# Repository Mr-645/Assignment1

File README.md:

Prab Singh - 2121645<br>MG7013 - Embedded Systems<br>16 May 2019
# Assignment 1 - Bubble display
## USAGE INSTRUCTIONS
1. Download and install the [Adafruit BMP085 Library](https://github.com/adafruit/Adafruit-BMP085-Library) for use with your Arduino compatible board.
2. If your setup is like mine (MOSFETs for the cathodes), find the `SevSeg.cpp` file of library and make [these](https://github.com/Mr-645/Assignment1#changes-to-sevsegcpp) modifications.
3. Download [this folder](https://github.com/Mr-645/Assignment1/tree/master/Assignment%201%20-%20Bubble%20display%20-%20Arduino%20Nano) (Assign 2 - Bubble Display - Arduino Nano) to get the Arduino sketch/C-programme
4. Navigate to the `/src` folder and run `main.cpp`.
## REPORT
### Project purpose and general description

**Make a Stopwatch** using a microcontroller, buttons, and a 7-segment array [Bubble display].

<!------>

*Criteria*: 
1. One `RESET` button + One `START/STOP` button
2. Bubble Display shows the time

*Rules*:
- Time measurement precision (max. 100ms in a 10s timespan)
- Proof the working debouncing of your buttons `REFER TO THE VIDEO FOR THIS PROOF`
- No delay() function
- Use of external interrupts
- Use the provided MOSFETs as the provided uC-Boards IOs can only
sink and source a limited current

---

### Description of design process steps

The Bubble display is of the type `Common Cathode`. This means that every segment in a single digit shares a ground pin (a cathode is a negative pin). What this equates to is that in order to turn off an entire digit, all you need to do is disconnect its ground. The [Adafruit BMP085 Library](https://github.com/adafruit/Adafruit-BMP085-Library) can take care of this for you.

The only problem was that: we weren't driving the common-cathode 7-segment array in the fashion that the library expected. The library expected a direct connection, but we had MOSFETs between the array's negative pins and the GND rail (the MOSFETs were a requirement due to the microcontroller's limited current handling capabilities). 

With a direct connection, the microcontroller set a `logic low` on the cathode (GND) pins of the array, but because of the MOSFETs, we needed the microcontroller to put out a `logic high` instead. So, a modification of the `SevSeg.cpp` file of library was required in order to make it compliant. 

#### Changes to <SevSeg.cpp>
The code segment we need to change lies around the line number 100 mark. It looked like this:
```C
if(mode == COMMON_ANODE)
  {
    DigitOn = HIGH;
    DigitOff = LOW;
    SegOn = LOW;
    SegOff = HIGH;
  }
  else {
    DigitOn = LOW;
    DigitOff = HIGH;
    SegOn = HIGH;
    SegOff = LOW;
  }
```
It was changed to this:
```C
if(mode == COMMON_ANODE)
  {
    DigitOn = HIGH;
    DigitOff = LOW;
    SegOn = LOW;
    SegOff = HIGH;
  }
  else {
  //-----------------------THE CHANGE WAS MADE BETWEEN HERE
    DigitOn = HIGH;
    DigitOff = LOW;
  //-----------------------AND HERE
    SegOn = HIGH;
    SegOff = LOW;
  }
``` 

#### Pin choice
I needed two pins with hardware interrupt capability to handle button presses. The Arduino Nano only has two hardware interrupt pins and they're both 'Digital Pins'. The 7-segment array is run by multiplexing its pins (a digital process). If I was to use only the digital pins for the array, I would have run since there are only so many of those pins. 

Fortunately most of the analogue pins could be used as digital pins so I ended up using the A0, A1, and A2 pins of the Nano for the array. There was no need for changing a configuration setting of any sort. The usage of the analogue pins was in the same way as it was with the digital pins. All that was required was pin declaration in the setup function with the digital pins.

#### Programme logic for making the stopwatch work properly
This code below is the heart of the stopwatch functionality. You only need three variables to do it.

The variables are:
```C
//Global variables
uint32_t startTimePoint = 0; //Point at which the stopwatch starts from a reset or the microcontroller turning on
uint32_t timeWhilstStopped = 0; //Tracks end time points for the latest stopped time period
uint32_t TimeOfStopWatch = 0; //Tracks the end time point for the latest run time period
```
This is the logic:
```C
// Main timing stuff starts here
  //Pressed start
  if(allowTiming == true){
    if(TimeOfStopWatch == 0){
      startTimePoint = millis(); //Keeps updating the start time point until start is pressed
      TimeOfStopWatch++; //This just gets the variable going for the loop to handle next time
    }
    else if(timeWhilstStopped == 0){
      TimeOfStopWatch = millis() - timeWhilstStopped - startTimePoint; //Main sums for stop watch running before the first stop
    }
    else{
      TimeOfStopWatch = millis() - timeWhilstStopped; //Main sums for all following stopwatch stop/starts
    }
  }
  //Pressed stop
  else if(allowTiming == false) {
    if(TimeOfStopWatch != 0){
      timeWhilstStopped = millis() - TimeOfStopWatch; //Keeps track of how long we were stopped for
    }
    else{
      timeWhilstStopped = 0; //Housekeeping for when the stopwatch is reset
    }
  }
```

---

### Component choice and Schematic

The Arduino Nano microcontroller and the bubble display can only handle so much current. 

The Nano can only handle 20 mA per pin, and 200 mA overall.
The bubble display can only handle 5 mA per segment and 0.5 mA per segment provides adequate brightness.
<span style="background-color: #FFFF00">`Datasheet is in appendix`

For circit safety I put a potentiometer in series in the GND line (source pins of the mosfets). What I did was dial the resistance down to control the current flow (and thereby the brightness) until adequate brightness was achieved. The pot resistance was 330 Ω.

Initially I put resistors in series for each anode (330 Ω) but considered removing them once I installed the potentiometer, eventually I left them in for extra safety.

For reliable performance I installed pulldown resistors on the mosfet gates (5.6 kΩ). The concern was with the potential for segment flickering during startup.

---

### Limitations of project and potential improvements
It worked really well most of the time. The timing, and the aspect of displaying values to the screen is perfect. Unfortunately, sometimes a glitch happens when a button is pressed. It doesn't happen very often, but it's not very rare either. 

The glitch is: the microcontroller registers a hardware interrupt and flashes the LED for debounce indication, but it doesn't run the code in the function.

I don't know how I'll implement an improvement to this system to sort out the glitch.

---

### Appendix
#### Datasheet and reference

<!------>
The Bubble display datasheet (BB_QDSP_DS.pdf) is available [here](/BB_QDSP_DS.pdf)

An infographic for the Nano is available [here](https://i.pinimg.com/736x/c4/87/21/c487213e9081fb0050878a02304e5693.jpg), it shows pin type information and current capability too. 

#### Source code of non-testing version of programme
The source code (main.cpp) is available [here](/Assignment%201%20-%20Bubble%20display%20-%20Arduino%20Nano/src/main.cpp)

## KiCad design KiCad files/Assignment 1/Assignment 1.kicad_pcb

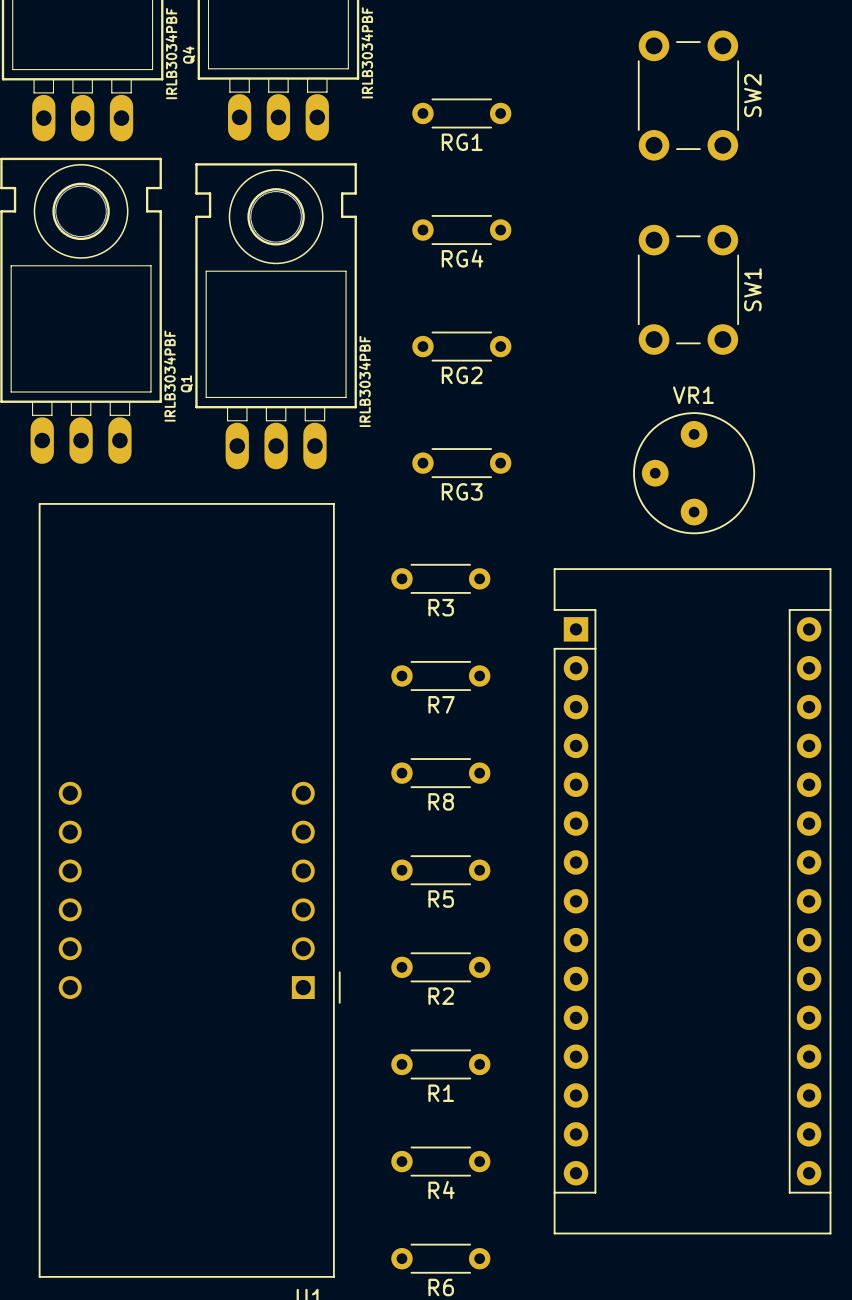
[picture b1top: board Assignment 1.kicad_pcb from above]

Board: 2 copper layers, 21 parts (0 on the bottom side), 24 nets, no tracks yet.

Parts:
A1: Arduino_Nano_v3.x; Arduino_Nano
Q1, Q2, Q3, Q4: IRLB3034PBF; TO-220-ALT
R1, R2, R3, R4, R5, R6, R7, R8: 330 Ω; R_Axial_DIN0204_L3.6mm_D1.6mm_P5.08mm_Horizontal
RG1, RG2, RG3, RG4: 5.6k; R_Axial_DIN0204_L3.6mm_D1.6mm_P5.08mm_Horizontal
SW1, SW2: SW_Push; SW_PUSH_6mm_H4.3mm
U1: CC56-12EWA; CA56-12EWA
VR1: POTENTIOMETER-PTH-9MM-1_20W-20%; Potentiometer_Bourns_3339P_Vertical_HandSoldering

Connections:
Digit_1_cathode: A1.13, RG1.1
Digit_2_cathode: A1.15, RG2.1
Digit_3_cathode: A1.14, RG3.1
Digit_4_cathode: A1.19, RG4.1
GND: A1.29, SW1.1, SW2.1
unnamed: A1.5, SW1.2
unnamed: A1.6, SW2.2
unnamed: RG1.2, RG2.2, RG3.2, RG4.2
unnamed: R1.2, U1.11
unnamed: R2.2, U1.4
unnamed: R3.2, U1.1
unnamed: R4.2, U1.5
unnamed: R5.2, U1.7
unnamed: R6.2, U1.2
unnamed: R7.2, U1.10
unnamed: R8.2, U1.3
Segment_A_anode: A1.20, R1.1
Segment_B_anode: A1.21, R5.1
Segment_C_anode: A1.7, R2.1
Segment_DP_anode: A1.12, R8.1
Segment_D_anode: A1.8, R6.1
Segment_E_anode: A1.9, R3.1
Segment_F_anode: A1.10, R7.1
Segment_G_anode: A1.11, R4.1

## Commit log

2019-05-13 Commit 1
2019-05-13 Added src folder usage instructions
2019-05-13 Added fully built prototype image and updated readme
2019-05-13 Added more instructions
2019-05-14 Fixed KiCad project file clash issue Added code to ReadMe
2019-05-14 Added images of the schematic and the 3D view
2019-05-14 Added more to readme. Added info to photo of porotoype and renamed it
2019-05-14 Fixed mark highlighting issues Fixed (hopefully) heading underlining issues
2019-05-14 Retry
2019-05-14 Retry 2
2019-05-14 Added gitignore
2019-05-14 fixed gitignore
2019-05-15 Added comments to code Added datasheet image Updated README file
2019-05-15 updated gitignore
2019-05-15 Removed folder for teensy version
2019-05-15 Added more to readme
2019-05-16 Almost finished README
2019-05-16 Final version of readme
2019-05-16 little fix
